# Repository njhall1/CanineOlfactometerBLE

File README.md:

# CanineOlfactometerBLE
Bluetooth Version of Canine Olfactometer

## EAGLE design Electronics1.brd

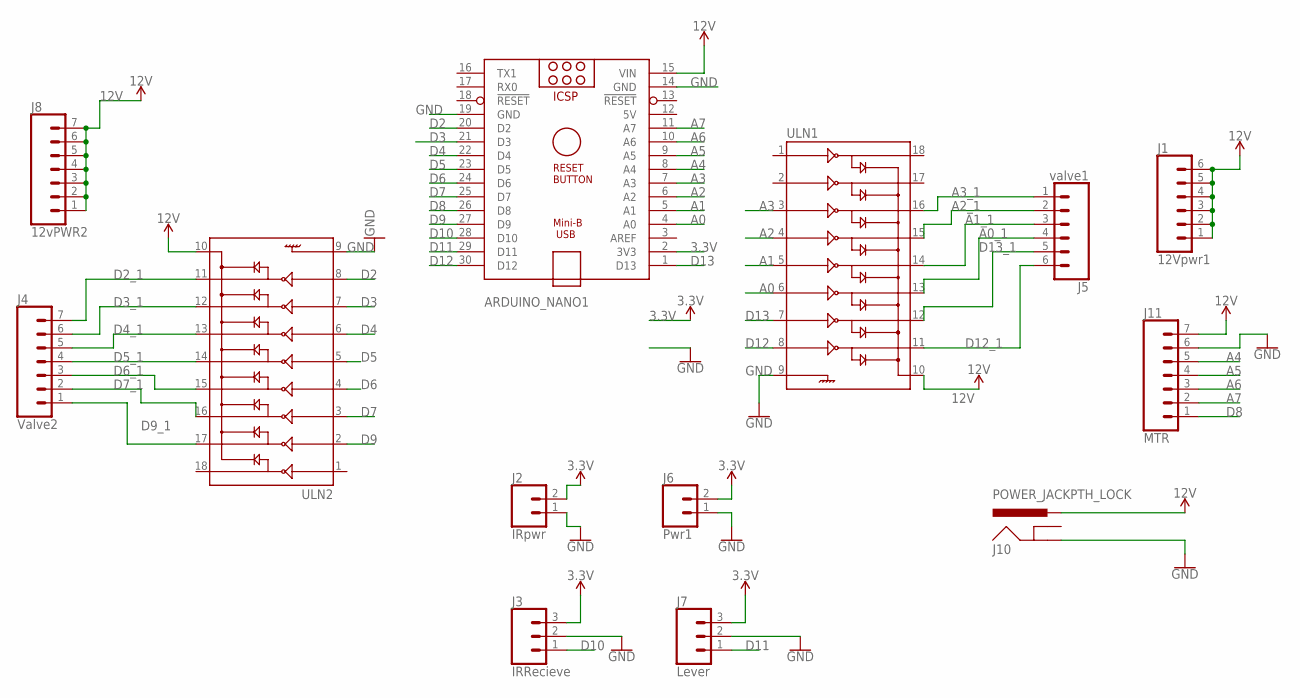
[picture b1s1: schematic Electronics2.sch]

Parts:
ARDUINO_NANO1: ARDUINO_NANO
J1: 12Vpwr1; 1X06_LOCK
J2: IRpwr; 1X02
J3: IRRecieve; 1X03
J4: Valve2; 1X07
J5: valve1; 1X06_LOCK
J6: Pwr1; 1X02
J7: Lever; 1X03
J8: 12vPWR2; 1X07
J10: POWER_JACKPTH_LOCK; POWER_JACK_PTH_LOCK
J11: MTR; 1X07
ULN1, ULN2: ULN2803DIP; DIL18

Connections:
3.3V: ARDUINO_NANO1.2 (3V3), J2.2, J3.3, J6.2, J7.3
5V: ARDUINO_NANO1.12 (5V)
12V: ARDUINO_NANO1.15 (VIN), J1.1, J1.2, J1.3, J1.4, J1.5, J1.6, J8.1, J8.2, J8.3, J8.4, J8.5, J8.6, J8.7, J10.PWR, J11.7, ULN1.10, ULN2.10
A0: ARDUINO_NANO1.4 (A0), ULN1.6
A0_1: J5.4, ULN1.13
A1: ARDUINO_NANO1.5 (A1), ULN1.5
A1_1: J5.3, ULN1.14
A2: ARDUINO_NANO1.6 (A2), ULN1.4
A2_1: J5.2, ULN1.15
A3: ARDUINO_NANO1.7 (A3), ULN1.3
A3_1: J5.1, ULN1.16
A4: ARDUINO_NANO1.8 (A4), J11.5
A5: ARDUINO_NANO1.9 (A5), J11.4
A6: ARDUINO_NANO1.10 (A6), J11.3
A7: ARDUINO_NANO1.11 (A7), J11.2
D2: ARDUINO_NANO1.20 (D2), ULN2.8
D2_1: J4.7, ULN2.11
D3: ARDUINO_NANO1.21 (D3), ULN2.7
D3_1: J4.6, ULN2.12
D4: ARDUINO_NANO1.22 (D4), ULN2.6
D4_1: J4.5, ULN2.13
D5: ARDUINO_NANO1.23 (D5), ULN2.5
D5_1: J4.4, ULN2.14
D6: ARDUINO_NANO1.24 (D6), ULN2.4
D6_1: J4.3, ULN2.15
D7: ARDUINO_NANO1.25 (D7), ULN2.3
D7_1: J4.2, ULN2.16
D8: ARDUINO_NANO1.26 (D8), J11.1
D9: ARDUINO_NANO1.27 (D9), ULN2.2
D9_1: J4.1, ULN2.17
D10: ARDUINO_NANO1.28 (D10), J3.1
D11: ARDUINO_NANO1.29 (D11), J7.1
D12: ARDUINO_NANO1.30 (D12), ULN1.8
D12_1: J5.6, ULN1.11
D13: ARDUINO_NANO1.1 (D13), ULN1.7
D13_1: J5.5, ULN1.12
GND: ARDUINO_NANO1.14 (GND), ARDUINO_NANO1.19 (GND), J2.1, J3.2, J6.1, J7.2, J10.GND, J11.6, ULN1.9, ULN2.9

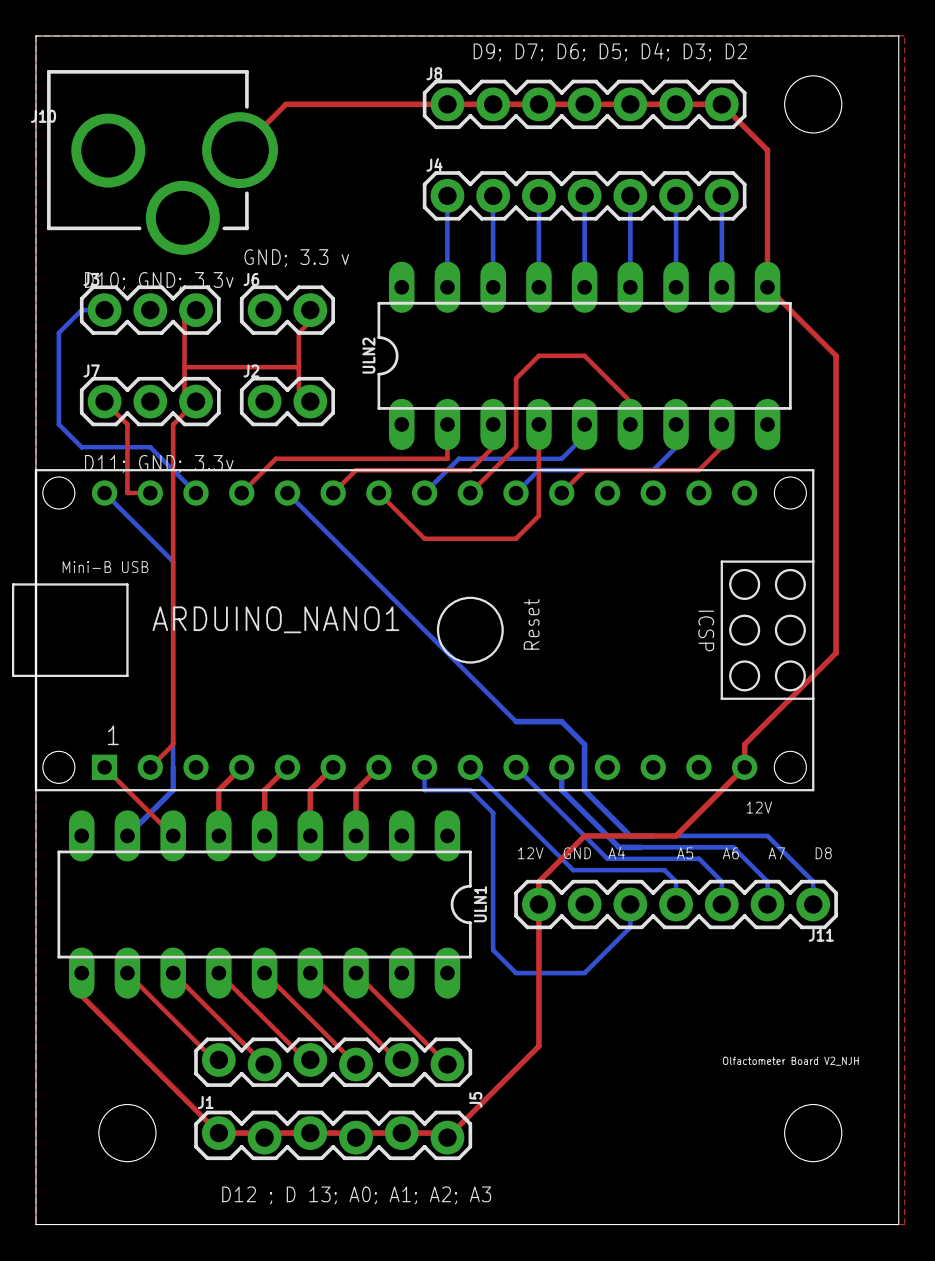
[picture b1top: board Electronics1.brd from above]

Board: 2 copper layers, 47.9 x 66.0 mm, 13 parts (0 on the bottom side), 36 nets.

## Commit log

2022-07-21 Upload BLE 4.1 code
2022-07-21 add arduino code
2022-07-25 add circuit boards
2023-01-25 Added multiple odor activation
2023-01-25 Delete Firmware_Olfactometer4_5.ino
    remove old firmware

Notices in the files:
parts and their libraries:
SparkFun-Connectors: Licensing: Creative Commons ShareAlike 4.0 International - https://creativecommons.org/licenses/by-sa/4.0
